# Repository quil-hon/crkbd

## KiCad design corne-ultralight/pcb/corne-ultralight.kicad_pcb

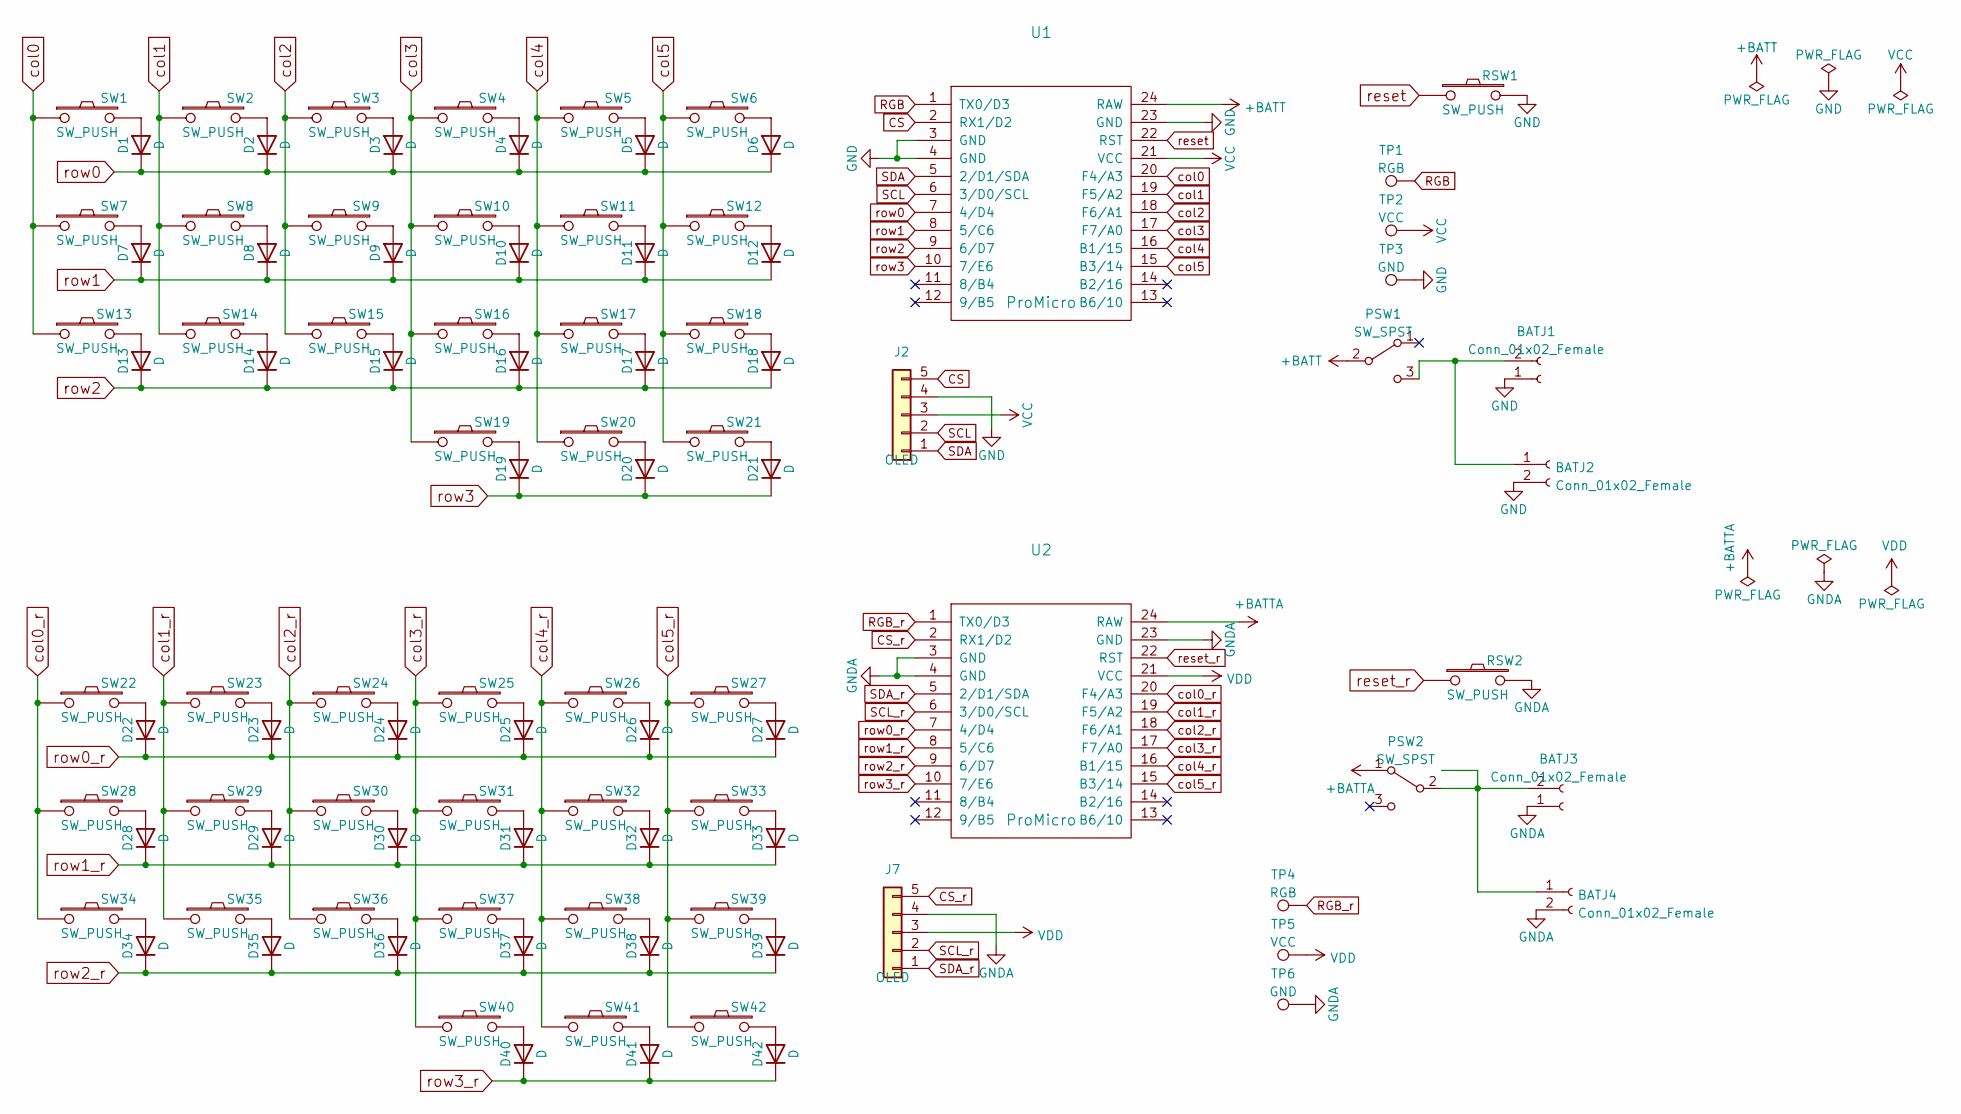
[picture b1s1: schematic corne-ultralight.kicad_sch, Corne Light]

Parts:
BATJ1, BATJ3: Conn_01x02_Female; PinHeader_1x02_P2.54mm_Vertical
BATJ2, BATJ4: Conn_01x02_Female; JST_PH_S2B-PH-K_1x02_P2.00mm_Horizontal
D1, D2, D3, D4, D5, D6, D7, D8, D9, D10, D11, D12, D13, D14, D15, D16, D17, D18, D19, D20, D21, D22, D23, D24, D25, D26, D27, D28, D29, D30, D31, D32, D33, D34, D35, D36, D37, D38, D39, D40, D41, D42: D; D3_TH
J2, J7: OLED; nice_view_1side
PSW1, PSW2: SW_SPST; SW_SPDT_PCM12
RSW1, RSW2: SW_PUSH; ResetSW_1side
SW1, SW2, SW3, SW4, SW5, SW6, SW7, SW8, SW9, SW10, SW11, SW12, SW13, SW14, SW15, SW16, SW17, SW18, SW19, SW20, SW22, SW23, SW24, SW25, SW26, SW27, SW28, SW29, SW30, SW31, SW32, SW33, SW34, SW35, SW36, SW37, SW38, SW39, SW40, SW41: SW_PUSH; SW_Hotswap_Kailh_Choc_V1V2
SW21, SW42: SW_PUSH; SW_Hotswap_Kailh_Choc_V1V2_1.50u
TP1, TP4: RGB; TestPoint_Pad_D1.5mm
TP2, TP5: VCC; TestPoint_Pad_D1.5mm
TP3, TP6: GND; TestPoint_Pad_D1.5mm
U1, U2: ProMicro; ProMicro_v3

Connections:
+BATT: PSW1.2 (B), U1.24 (RAW)
+BATTA: PSW2.1 (A), U2.24 (RAW)
CS: J2.5, U1.2 (RX1/D2)
CS_r: J7.5, U2.2 (RX1/D2)
GND: BATJ1.1, BATJ2.2, J2.4, RSW1.2, TP3.1, U1.3 (GND), U1.4 (GND), U1.23 (GND)
GNDA: BATJ3.1, BATJ4.2, J7.4, RSW2.2, TP6.1, U2.3 (GND), U2.4 (GND), U2.23 (GND)
unnamed: BATJ1.2, BATJ2.1, PSW1.3 (C)
unnamed: BATJ3.2, BATJ4.1, PSW2.2 (B)
unnamed: D1.2 (A), SW1.2
unnamed: D2.2 (A), SW2.2
unnamed: D3.2 (A), SW3.2
unnamed: D4.2 (A), SW4.2
unnamed: D5.2 (A), SW5.2
unnamed: D6.2 (A), SW6.2
unnamed: D7.2 (A), SW7.2
unnamed: D8.2 (A), SW8.2
unnamed: D9.2 (A), SW9.2
unnamed: D10.2 (A), SW10.2
unnamed: D11.2 (A), SW11.2
unnamed: D12.2 (A), SW12.2
unnamed: D13.2 (A), SW13.2
unnamed: D14.2 (A), SW14.2
unnamed: D15.2 (A), SW15.2
unnamed: D16.2 (A), SW16.2
unnamed: D17.2 (A), SW17.2
unnamed: D18.2 (A), SW18.2
unnamed: D19.2 (A), SW19.2
unnamed: D20.2 (A), SW20.2
unnamed: D21.2 (A), SW21.2
unnamed: D22.2 (A), SW22.2
unnamed: D23.2 (A), SW23.2
unnamed: D24.2 (A), SW24.2
unnamed: D25.2 (A), SW25.2
unnamed: D26.2 (A), SW26.2
unnamed: D27.2 (A), SW27.2
unnamed: D28.2 (A), SW28.2
unnamed: D29.2 (A), SW29.2
unnamed: D30.2 (A), SW30.2
unnamed: D31.2 (A), SW31.2
unnamed: D32.2 (A), SW32.2
unnamed: D33.2 (A), SW33.2
unnamed: D34.2 (A), SW34.2
unnamed: D35.2 (A), SW35.2
unnamed: D36.2 (A), SW36.2
unnamed: D37.2 (A), SW37.2
unnamed: D38.2 (A), SW38.2
unnamed: D39.2 (A), SW39.2
unnamed: D40.2 (A), SW40.2
unnamed: D41.2 (A), SW41.2
unnamed: D42.2 (A), SW42.2
RGB: TP1.1, U1.1 (TX0/D3)
RGB_r: TP4.1, U2.1 (TX0/D3)
SCL: J2.2, U1.6 (3/D0/SCL)
SCL_r: J7.2, U2.6 (3/D0/SCL)
SDA: J2.1, U1.5 (2/D1/SDA)
SDA_r: J7.1, U2.5 (2/D1/SDA)
VCC: J2.3, TP2.1, U1.21 (VCC)
VDD: J7.3, TP5.1, U2.21 (VCC)
col0: SW1.1, SW7.1, SW13.1, U1.20 (F4/A3)
col0_r: SW22.1, SW28.1, SW34.1, U2.20 (F4/A3)
col1: SW2.1, SW8.1, SW14.1, U1.19 (F5/A2)
col1_r: SW23.1, SW29.1, SW35.1, U2.19 (F5/A2)
col2: SW3.1, SW9.1, SW15.1, U1.18 (F6/A1)
col2_r: SW24.1, SW30.1, SW36.1, U2.18 (F6/A1)
col3: SW4.1, SW10.1, SW16.1, SW19.1, U1.17 (F7/A0)
col3_r: SW25.1, SW31.1, SW37.1, SW40.1, U2.17 (F7/A0)
col4: SW5.1, SW11.1, SW17.1, SW20.1, U1.16 (B1/15)
col4_r: SW26.1, SW32.1, SW38.1, SW41.1, U2.16 (B1/15)
col5: SW6.1, SW12.1, SW18.1, SW21.1, U1.15 (B3/14)
col5_r: SW27.1, SW33.1, SW39.1, SW42.1, U2.15 (B3/14)
reset: RSW1.1, U1.22 (RST)
reset_r: RSW2.1, U2.22 (RST)
row0: D1.1 (K), D2.1 (K), D3.1 (K), D4.1 (K), D5.1 (K), D6.1 (K), U1.7 (4/D4)
row0_r: D22.1 (K), D23.1 (K), D24.1 (K), D25.1 (K), D26.1 (K), D27.1 (K), U2.7 (4/D4)
row1: D7.1 (K), D8.1 (K), D9.1 (K), D10.1 (K), D11.1 (K), D12.1 (K), U1.8 (5/C6)
row1_r: D28.1 (K), D29.1 (K), D30.1 (K), D31.1 (K), D32.1 (K), D33.1 (K), U2.8 (5/C6)
row2: D13.1 (K), D14.1 (K), D15.1 (K), D16.1 (K), D17.1 (K), D18.1 (K), U1.9 (6/D7)
row2_r: D34.1 (K), D35.1 (K), D36.1 (K), D37.1 (K), D38.1 (K), D39.1 (K), U2.9 (6/D7)
row3: D19.1 (K), D20.1 (K), D21.1 (K), U1.10 (7/E6)
row3_r: D40.1 (K), D41.1 (K), D42.1 (K), U2.10 (7/E6)

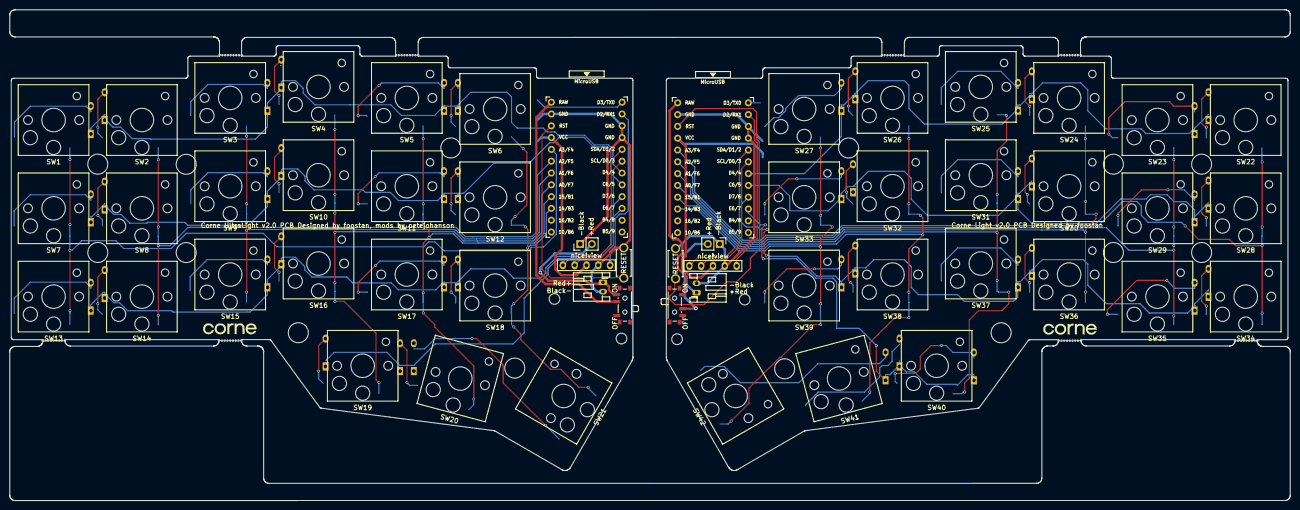
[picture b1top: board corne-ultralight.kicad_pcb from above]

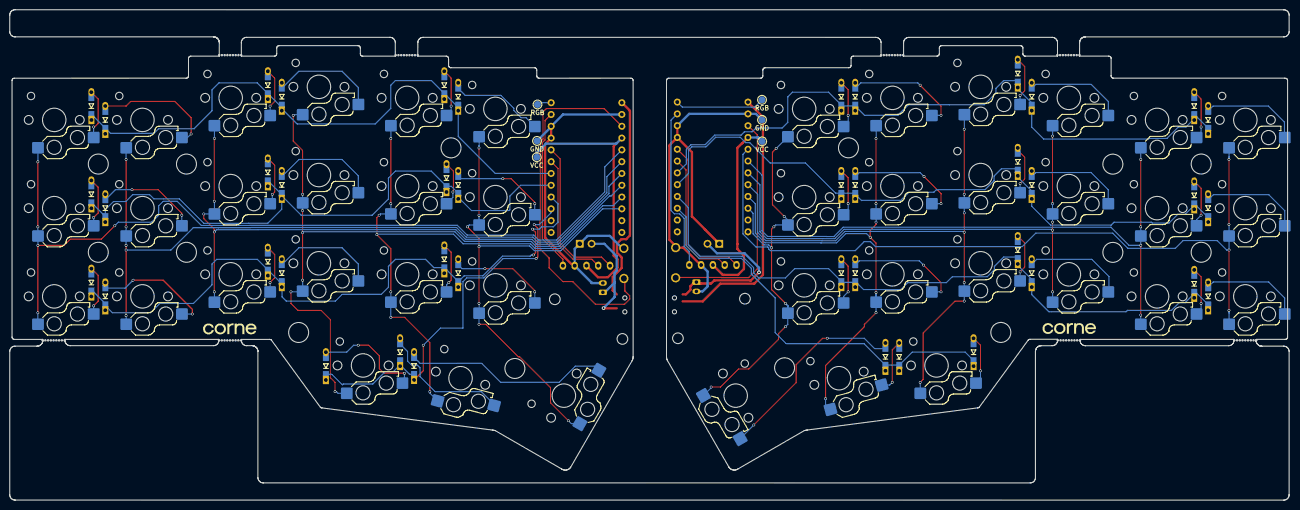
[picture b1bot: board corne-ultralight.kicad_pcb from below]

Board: 2 copper layers, 275.5 x 105.6 mm, 128 parts (64 on the bottom side), 80 nets.

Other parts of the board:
J5, J5#2, J5#3, J5#4, J5#5, J5#6, J5#7, J5#8: Breakaway_Tabs
Ref**: Val**; thread_m2
Ref**#2, Ref**#8, Ref**#9: Val**; thread_m2
Ref**#3, Ref**#4, Ref**#5, Ref**#6, Ref**#7, Ref**#10, Ref**#11, Ref**#12, Ref**#13, Ref**#14, Ref**#15, Ref**#16, Ref**#17, Ref**#18: Val**; spacer_m2

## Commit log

2022-06-21 Initial corne-ultralight board.
    * Power switch and battery pin/JST instead of TRRS.
    * Gateron ks-27, choc v1, and MX support.
2022-06-21 Adjust JST polarity.
2022-06-21 More silk/JST fixes.
2022-06-27 Add test points for RGB strip.
2022-10-12 Switch to nice!view display header.
    * Route extra pin and move header to be centered for
    nice!view display support.
2022-10-12 Consistent power switch on/off direction.
2023-04-24 Fix hybrid footprint for 5-pin MX switches.
2024-07-11 feat: switch to hotswap
2024-07-11 fix: correct the routing problem
2024-07-19 chore: correct the name for the wireless chocolate
2025-02-18 feat: add the support for 3x5
